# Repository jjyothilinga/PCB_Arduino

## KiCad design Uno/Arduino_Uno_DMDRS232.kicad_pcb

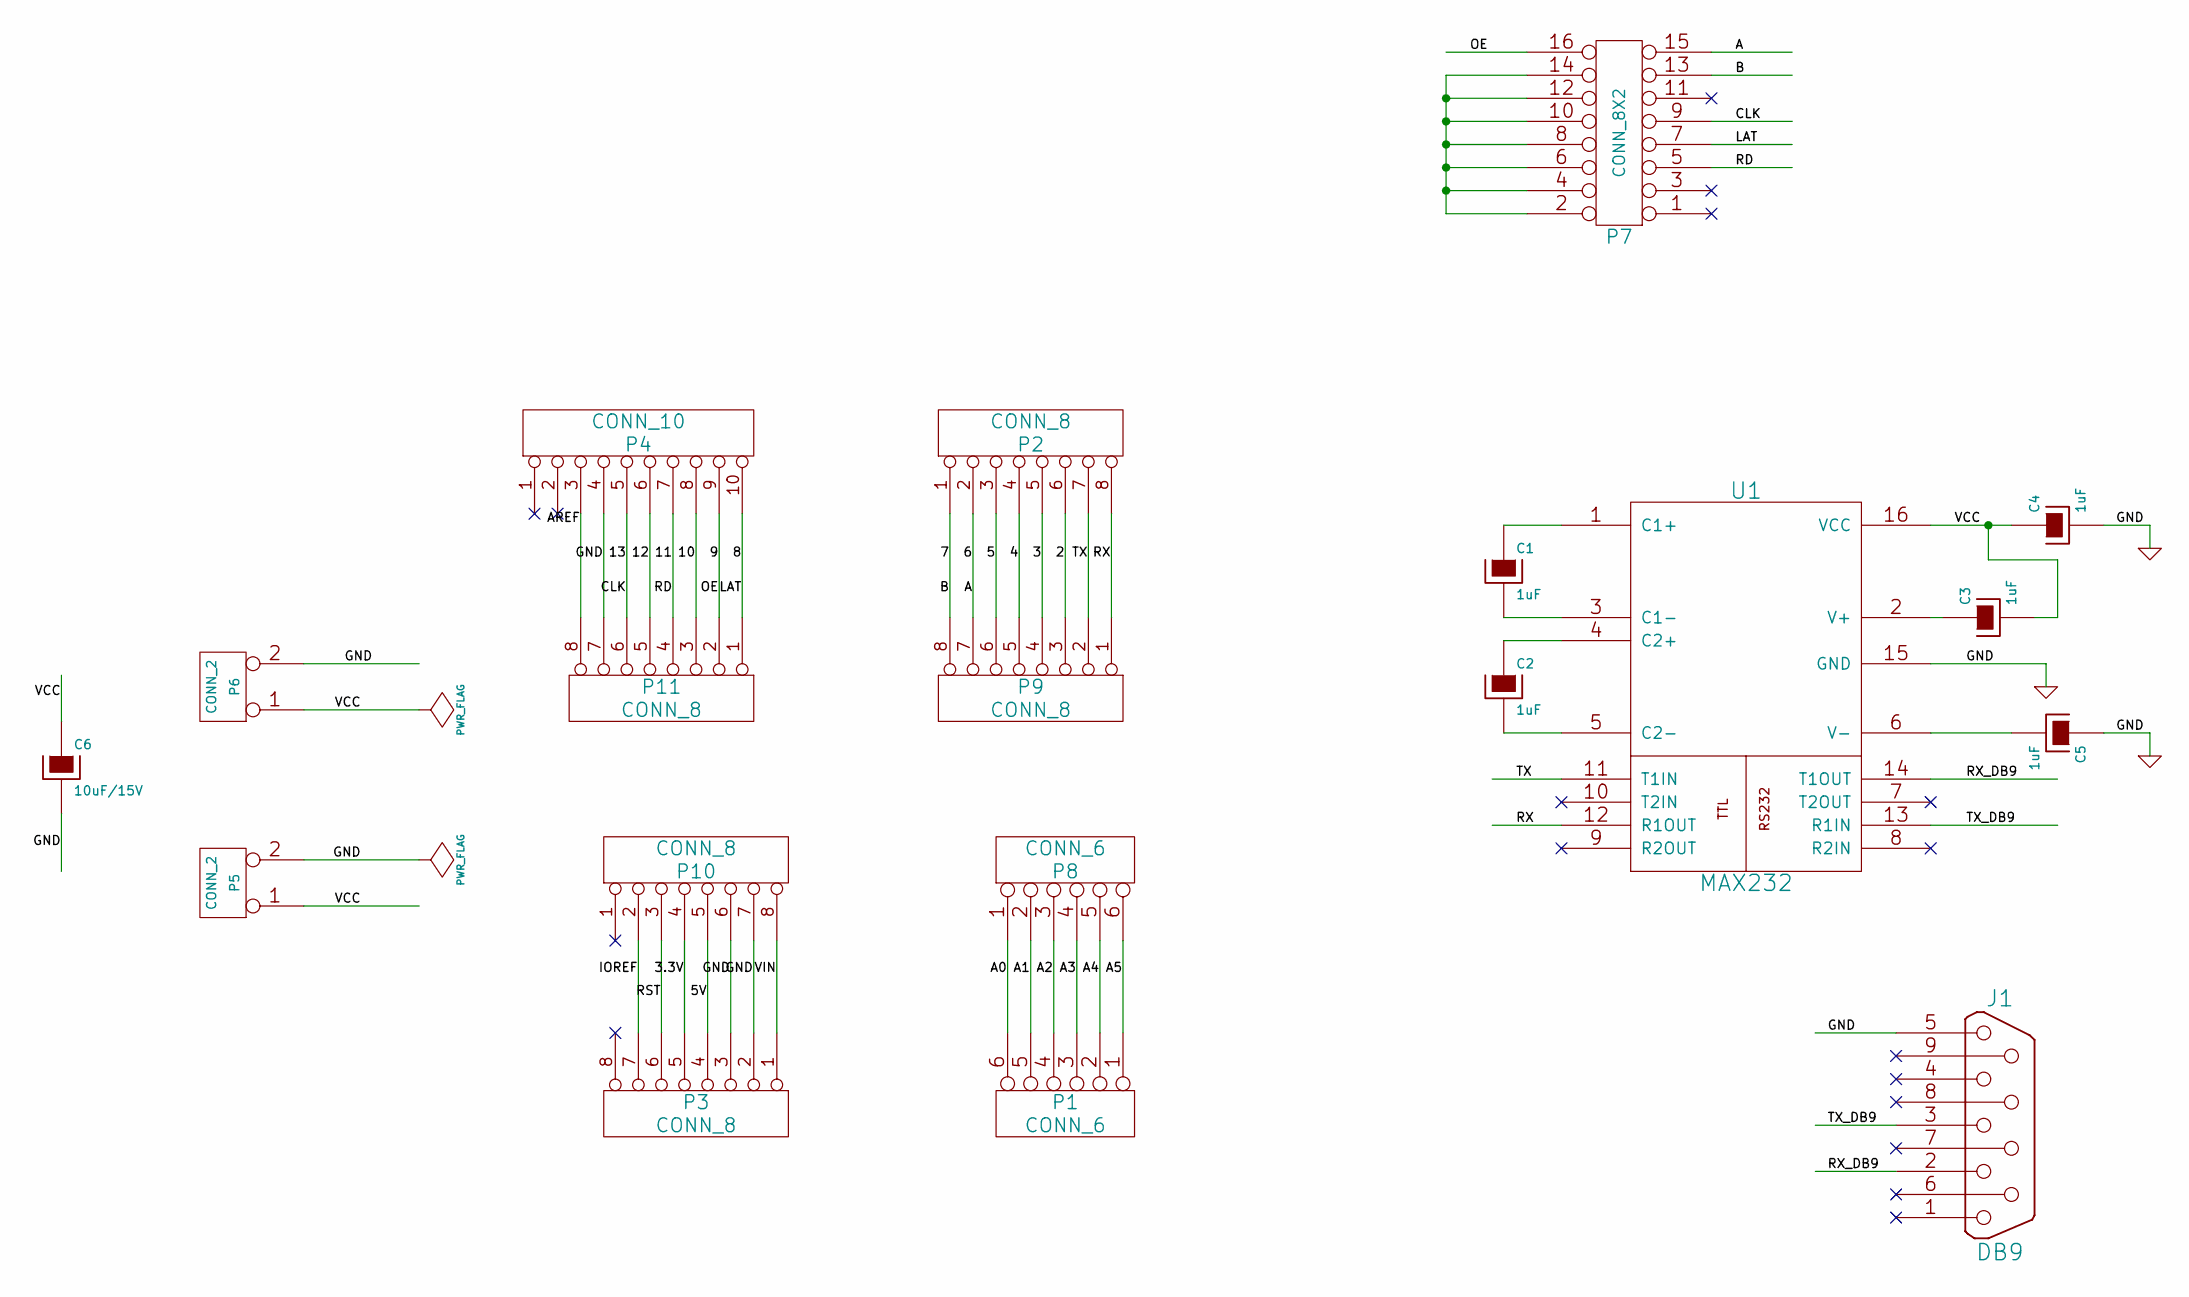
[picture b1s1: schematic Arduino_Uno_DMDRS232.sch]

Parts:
C1, C2, C3, C4, C5: 1uF
C6: 10uF/15V
J1: DB9
P1, P8: CONN_6
P2, P3, P9, P10, P11: CONN_8
P4: CONN_10
P5, P6: CONN_2
P7: CONN_8X2
U1: MAX232

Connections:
/2: P2.6, P9.3
/3: P2.5, P9.4
/3.3V: P3.5, P10.4
/4: P2.4, P9.5
/5: P2.3, P9.6
/5V: P3.4, P10.5
/6: P2.2, P7.15, P9.7
/7: P2.1, P7.13, P9.8
/8: P4.10, P7.7, P11.1
/9: P4.9, P7.16, P11.2
/10: P4.8, P11.3
/11: P4.7, P7.5, P11.4
/12: P4.6, P11.5
/13: P4.5, P7.9, P11.6
/A0: P1.6, P8.1
/A1: P1.5, P8.2
/A2: P1.4, P8.3
/A3: P1.3, P8.4
/A4: P1.2, P8.5
/A5: P1.1, P8.6
/AREF: P4.3, P11.8
/IOREF: P3.7, P10.2
/RST: P3.6, P10.3
/RX: P2.8, P9.1, U1.12 (R1OUT)
/RX_DB9: J1.2, U1.14 (T1OUT)
/TX: P2.7, P9.2, U1.11 (T1IN)
/TX_DB9: J1.3, U1.13 (R1IN)
/VCC: C3.2, C4.1, C6.1, P5.1, P6.1, U1.16 (VCC)
/VIN: P3.1, P10.8
GND: C4.2, C5.1, C6.2, J1.5, P3.2, P3.3, P4.4, P5.2 (PM), P6.2 (PM), P10.6, P10.7, P11.7, U1.15 (GND)
unnamed: C2.2, U1.5 (C2-)
unnamed: C3.1, U1.2 (V+)
unnamed: C5.2, U1.6 (V-)
unnamed: C2.1, U1.4 (C2+)
unnamed: C1.2, U1.3 (C1-)
unnamed: C1.1, U1.1 (C1+)
unnamed: P7.2, P7.4, P7.6, P7.8, P7.10, P7.12, P7.14

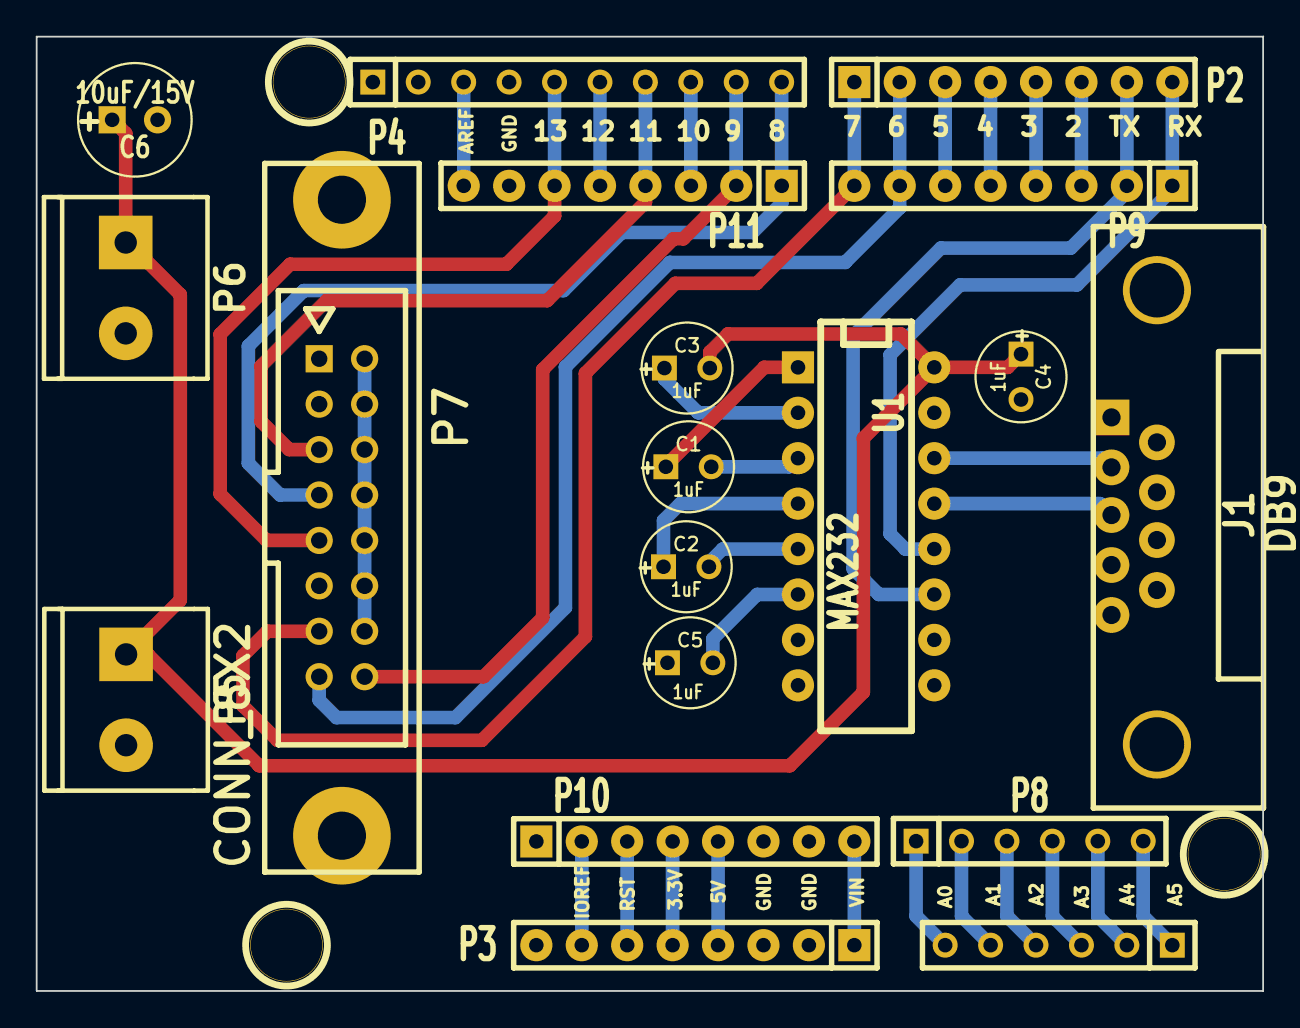
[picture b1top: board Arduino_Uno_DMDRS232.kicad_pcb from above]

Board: 2 copper layers, 68.6 x 53.4 mm, 22 parts (0 on the bottom side), 37 nets.

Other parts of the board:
1PIN, 1PIN#2, 1PIN#3: P***; 1pin

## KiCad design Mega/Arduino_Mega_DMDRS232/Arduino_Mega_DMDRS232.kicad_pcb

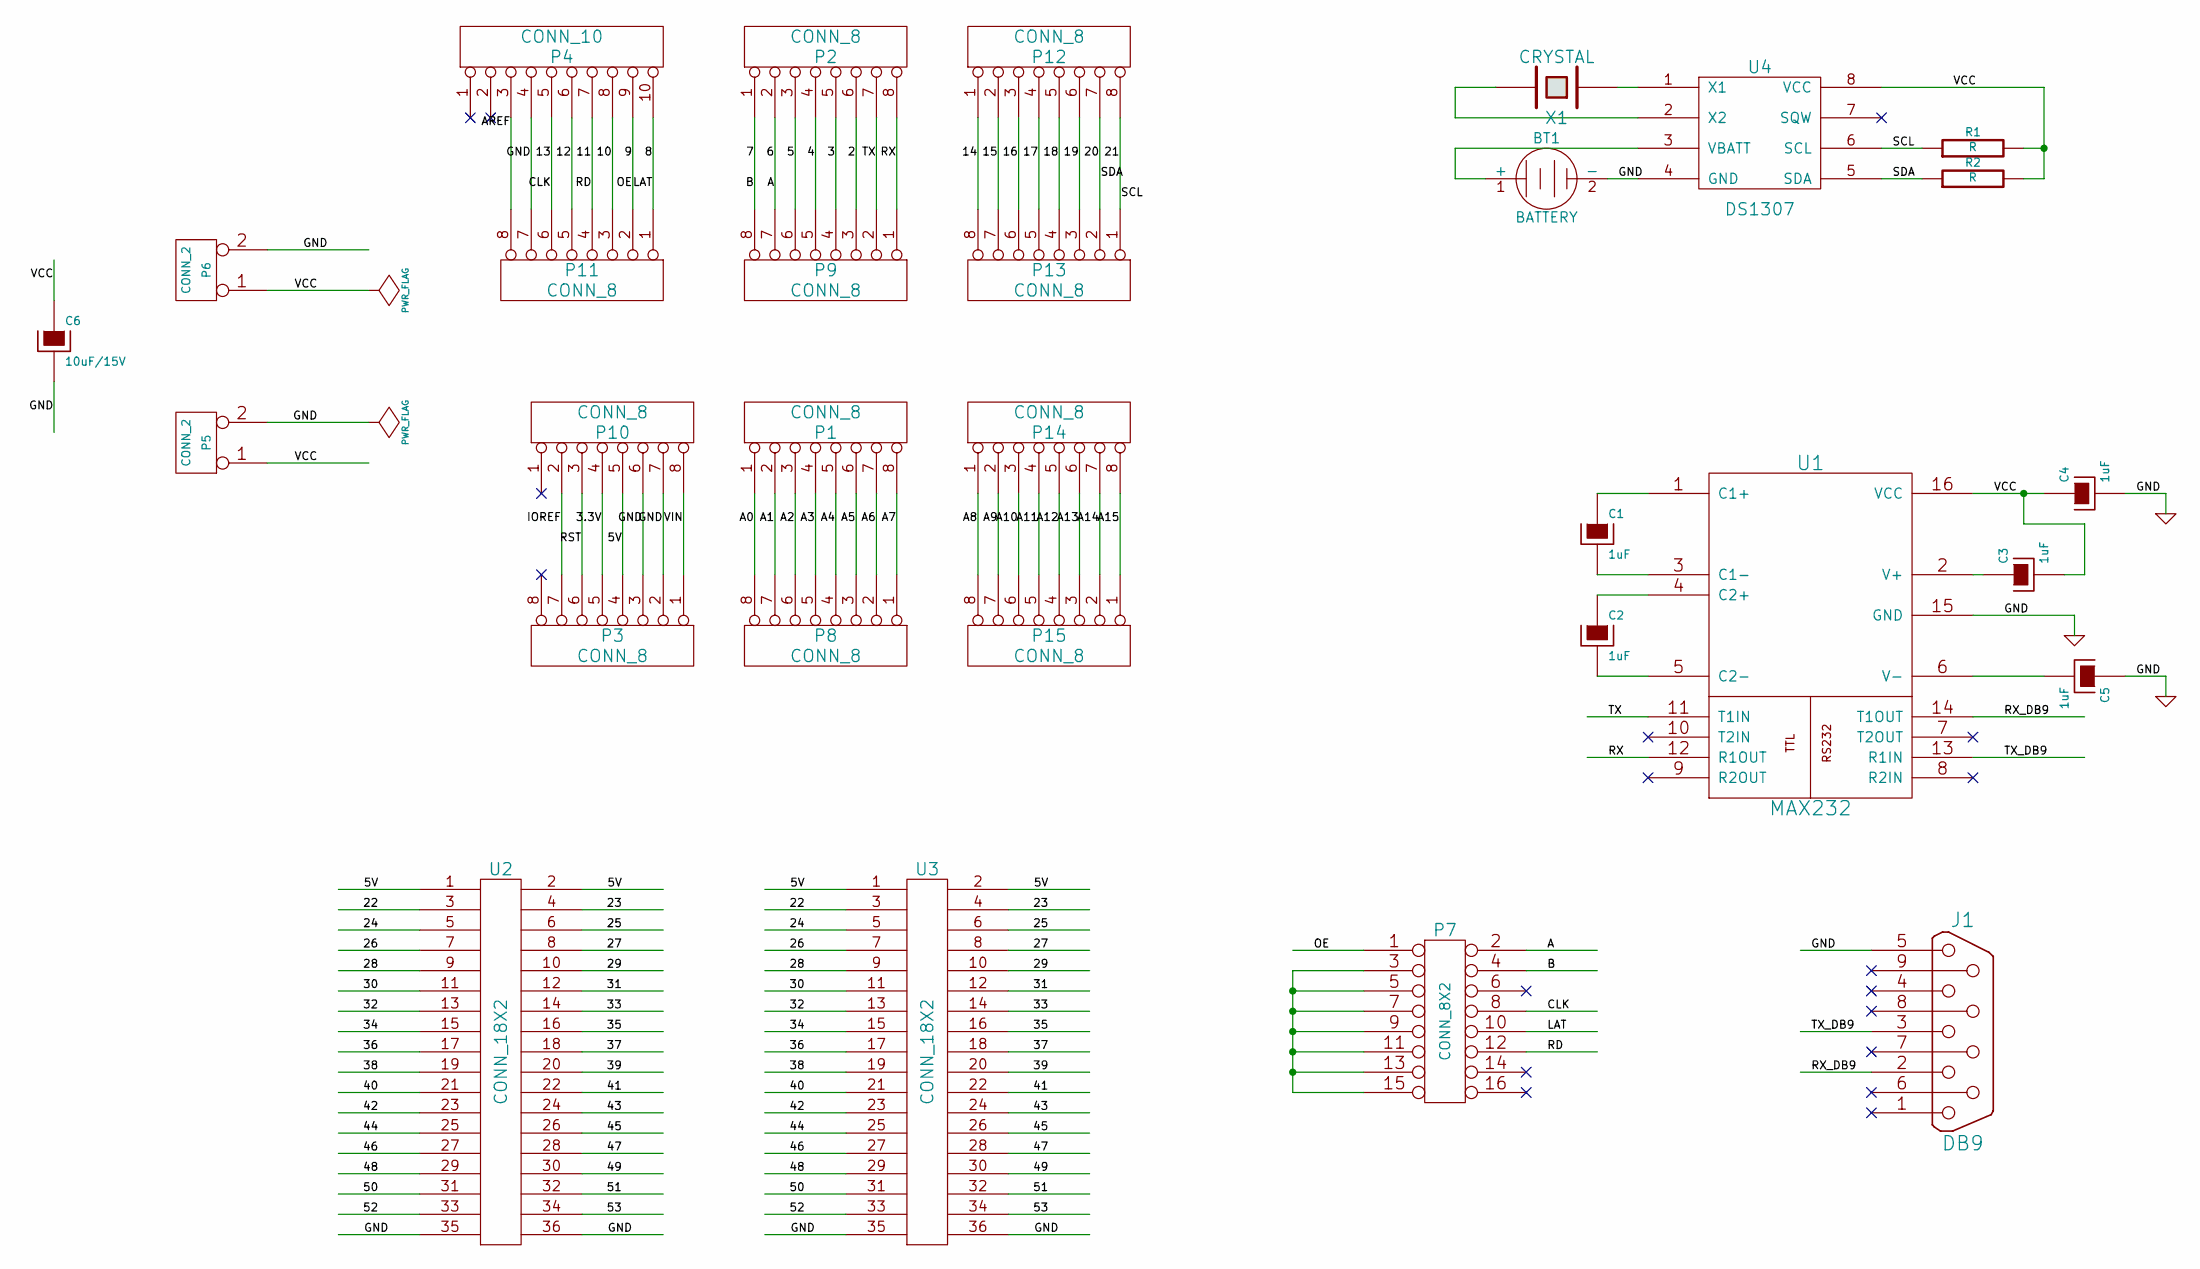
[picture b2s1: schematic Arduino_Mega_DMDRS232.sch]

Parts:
BT1: BATTERY
C1, C2, C3, C4, C5: 1uF
C6: 10uF/15V
J1: DB9
P1, P2, P3, P8, P9, P10, P11, P12, P13, P14, P15: CONN_8
P4: CONN_10
P5, P6: CONN_2
P7: CONN_8X2
R1, R2: R
U1: MAX232
U2, U3: CONN_18X2
U4: DS1307
X1: CRYSTAL

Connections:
/2: P2.6, P9.3
/3: P2.5, P9.4
/3.3V: P3.5, P10.4
/4: P2.4, P9.5
/5: P2.3, P9.6
/5V: P3.4, P10.5, U2.1, U2.2, U3.1, U3.2
/6: P2.2, P7.2, P9.7
/7: P2.1, P7.4, P9.8
/8: P4.10, P7.10, P11.1
/9: P4.9, P7.1, P11.2
/10: P4.8, P11.3
/11: P4.7, P7.12, P11.4
/12: P4.6, P11.5
/13: P4.5, P7.8, P11.6
/14: P12.1, P13.8
/15: P12.2, P13.7
/16: P12.3, P13.6
/17: P12.4, P13.5
/18: P12.5, P13.4
/19: P12.6, P13.3
/20: P12.7, P13.2, R2.1, U4.5 (SDA)
/21: P12.8, P13.1, R1.1, U4.6 (SCL)
/22: U2.3, U3.3
/23: U2.4, U3.4
/24: U2.5, U3.5
/25: U2.6, U3.6
/26: U2.7, U3.7
/27: U2.8, U3.8
/28: U2.9, U3.9
/29: U2.10, U3.10
/30: U2.11, U3.11
/31: U2.12, U3.12
/32: U2.13, U3.13
/33: U2.14, U3.14
/34: U2.15, U3.15
/35: U2.16, U3.16
/36: U2.17, U3.17
/37: U2.18, U3.18
/38: U2.19, U3.19
/39: U2.20, U3.20
/40: U2.21, U3.21
/41: U2.22, U3.22
/42: U2.23, U3.23
/43: U2.24, U3.24
/44: U2.25, U3.25
/45: U2.26, U3.26
/46: U2.27, U3.27
/47: U2.28, U3.28
/48: U2.29, U3.29
/49: U2.30, U3.30
/50: U2.31, U3.31
/51: U2.32, U3.32
/52: U2.33, U3.33
/53: U2.34, U3.34
/A0: P1.1, P8.8
/A1: P1.2, P8.7
/A2: P1.3, P8.6
/A3: P1.4, P8.5
/A4: P1.5, P8.4
/A5: P1.6, P8.3
/A6: P1.7, P8.2
/A7: P1.8, P8.1
/A8: P14.1, P15.8
/A9: P14.2, P15.7
/A10: P14.3, P15.6
/A11: P14.4, P15.5
/A12: P14.5, P15.4
/A13: P14.6, P15.3
/A14: P14.7, P15.2
/A15: P14.8, P15.1
/AREF: P4.3, P11.8
/IOREF: P3.7, P10.2
/RST: P3.6, P10.3
/RX: P2.8, P9.1, U1.12 (R1OUT)
/RX_DB9: J1.2, U1.14 (T1OUT)
/TX: P2.7, P9.2, U1.11 (T1IN)
/TX_DB9: J1.3, U1.13 (R1IN)
/VCC: C3.2, C4.1, C6.1, P5.1, P6.1, R1.2, R2.2, U1.16 (VCC), U4.8 (VCC)
/VIN: P3.1, P10.8
GND: BT1.2 (-), C4.2, C5.1, C6.2, J1.5, P3.2, P3.3, P4.4, P5.2 (PM), P6.2 (PM), P10.6, P10.7, P11.7, U1.15 (GND), U2.35, U2.36, U3.35, U3.36, U4.4 (GND)
unnamed: U4.1 (X1), X1.1
unnamed: U4.2 (X2), X1.2
unnamed: BT1.1 (+), U4.3 (VBATT)
unnamed: C1.2, U1.3 (C1-)
unnamed: C2.1, U1.4 (C2+)
unnamed: C2.2, U1.5 (C2-)
unnamed: C5.2, U1.6 (V-)
unnamed: C3.1, U1.2 (V+)
unnamed: C1.1, U1.1 (C1+)
unnamed: P7.3, P7.5, P7.7, P7.9, P7.11, P7.13, P7.15

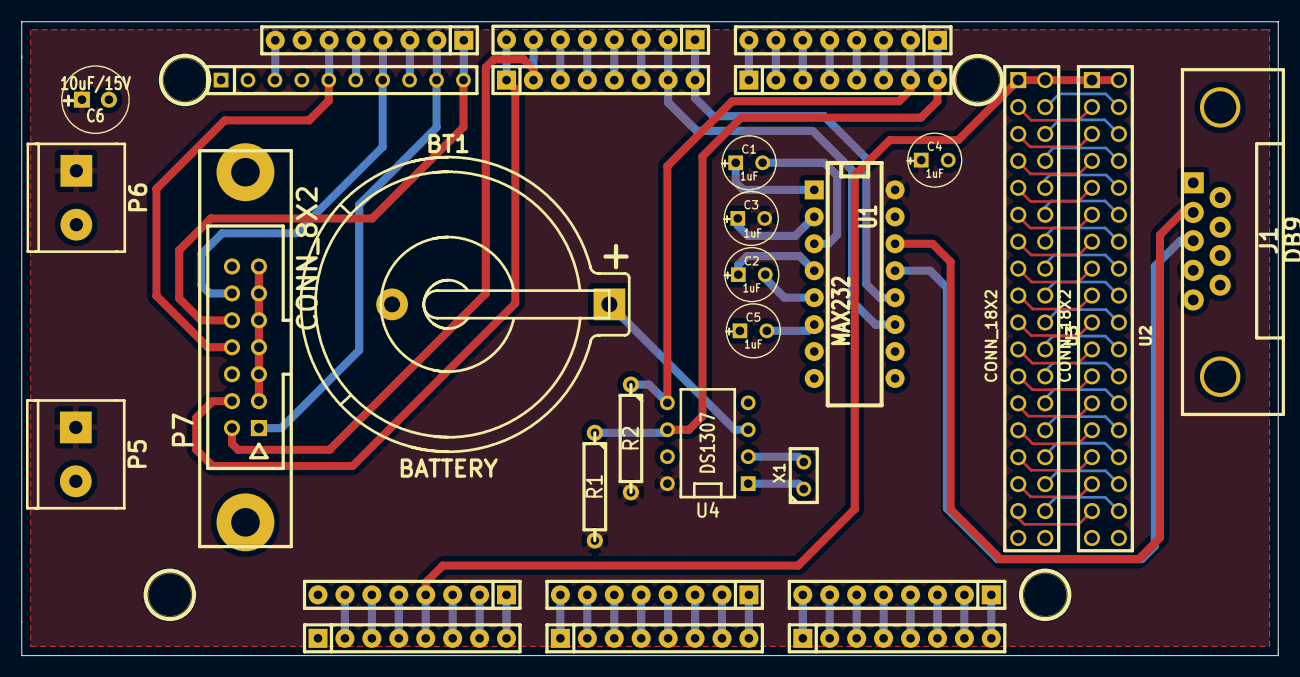
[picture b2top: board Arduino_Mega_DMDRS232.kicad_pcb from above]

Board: 2 copper layers, 118.5 x 59.8 mm, 34 parts (0 on the bottom side), 90 nets.

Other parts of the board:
1PIN, 1PIN#2, 1PIN#3, 1PIN#4: P***; 1pin

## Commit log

2015-10-15 :lollipop: Added .gitattributes & .gitignore files
2015-10-15 Completed
